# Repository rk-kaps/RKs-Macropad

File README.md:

<h1 align="center">RKs Macropad</h1>

<p align="center">
  Welcome to RKs Macropad, my custom 3D printed Macropad that runs KMK firmware.
</p>

<hr>
<h2>PCB & Schematic</h2>
<p align="center">
  
  <br><em>PCB Layout (KiCad)</em>
</p>
<p align="center">
  
  <br><em>Schematic</em>
</p>
<p align="center">
  
  <br><em>PCB 3D Render</em>
</p>

<h2>Motivation</h2>
<ul>>
MacroPad began as a simple rotary encoder-based volume controller. It evolved into a fully-featured macropad focused on:

Speeding up workflows
Reducing repetitive actions
Providing intuitive visual feedback
Maximizing functionality within hardware constraints
</ul>
</h2>
<h2> Project Highlights  </h2>
<ul>
- Efficient use of limited GPIO resources  
- Custom analog decoding for rotary encoder  
- Integration of hardware + firmware + UI design  
- Fully functional productivity tool
</ul>
<hr>

<h2>Bill of Materials:</h2>

<ul>
  <li>1x Rks Macropad PCB</li>
  <li>1x XIAO-PR2040-DIP</li>
  <li>1x EC11 rotary encoder</li>
  <li>11x Cherry MX (or equivalent) keyswitches</li>
  <li>11x Keycaps</li>
  <li>12x 1N4148 Throughhole diodes</li>
  <li>1x 0.91 inch OLED display (SSD1306 I2C 0.91 128x32)</li>
  <li>4x Cap head M3x16 machine screws</li>
  <li>1x 3D printed shell top half</li>
  <li>1x 3D printed shell bottom half</li>
</ul>

<p>
  small amount of spare wire apprx. 50mm worth.
</p>
<hr>
<h2>Instructions for Assembly</h2>
<ol>
  <li>Solder RP2040 directly onto the PCB without a header.</li>
  <li>Solder on diodes aligning with the silkscreen.</li>
  <li>Solder Cherry MX switches to board.</li>
  <li>
    Solder breakout cables to the spare 4 pins near the RP2040 — these will be used to wire to the OLED display.
    Make these breakout cables ~2" to allow for easier soldering.
  </li>
  <li>
    Clamshell the base around the PCB, passing the breakout cables through the small hole in the gap for the display
    in the top half of the case, then use the M3x16 machine screws to clamp the assembly together.
  </li>
  <li>Solder display to the breakout cables.</li>
  <li>Use double-sided tape or a light adhesive to hold the OLED into its holder.</li>
</ol>
<hr>
<h2>Acknowledgements</h2>
<ul>
- KMK Firmware Community  
- Good people of Hack Club
</ul>
<hr>

<h2>Instructions for Assembly:</h2>

<ol>
  <li>Solder RP2040 directly onto the pcb without a header.</li>
  <li>Solder on Diodes aligning with the slikscreen.</li>
  <li>Solder CherryMX switches to board.</li>
  <li>
    Solder breakout cables to the spare 4 pins near the RP2040, these will be used to wire to the OLED display.
    Make these breakout cables ~2" to allow for easier soledering.
  </li>
  <li>
    Clamshell the base around the PCB, passing the breakout cables through the small hole in the gap for the display
    in the top half of the case, then use the M3x16 machine screws to clamp the assembly together.
  </li>

  <li>Solder display to the breakout cables</li>
  <li>Use double-sided tape or a light adhesive to hold the OLED into its holder,.</li>

<h2> Acknowledgements  </h2>
<ul>
- KMK Firmware Community  
- Good people of Hack Club</ul>

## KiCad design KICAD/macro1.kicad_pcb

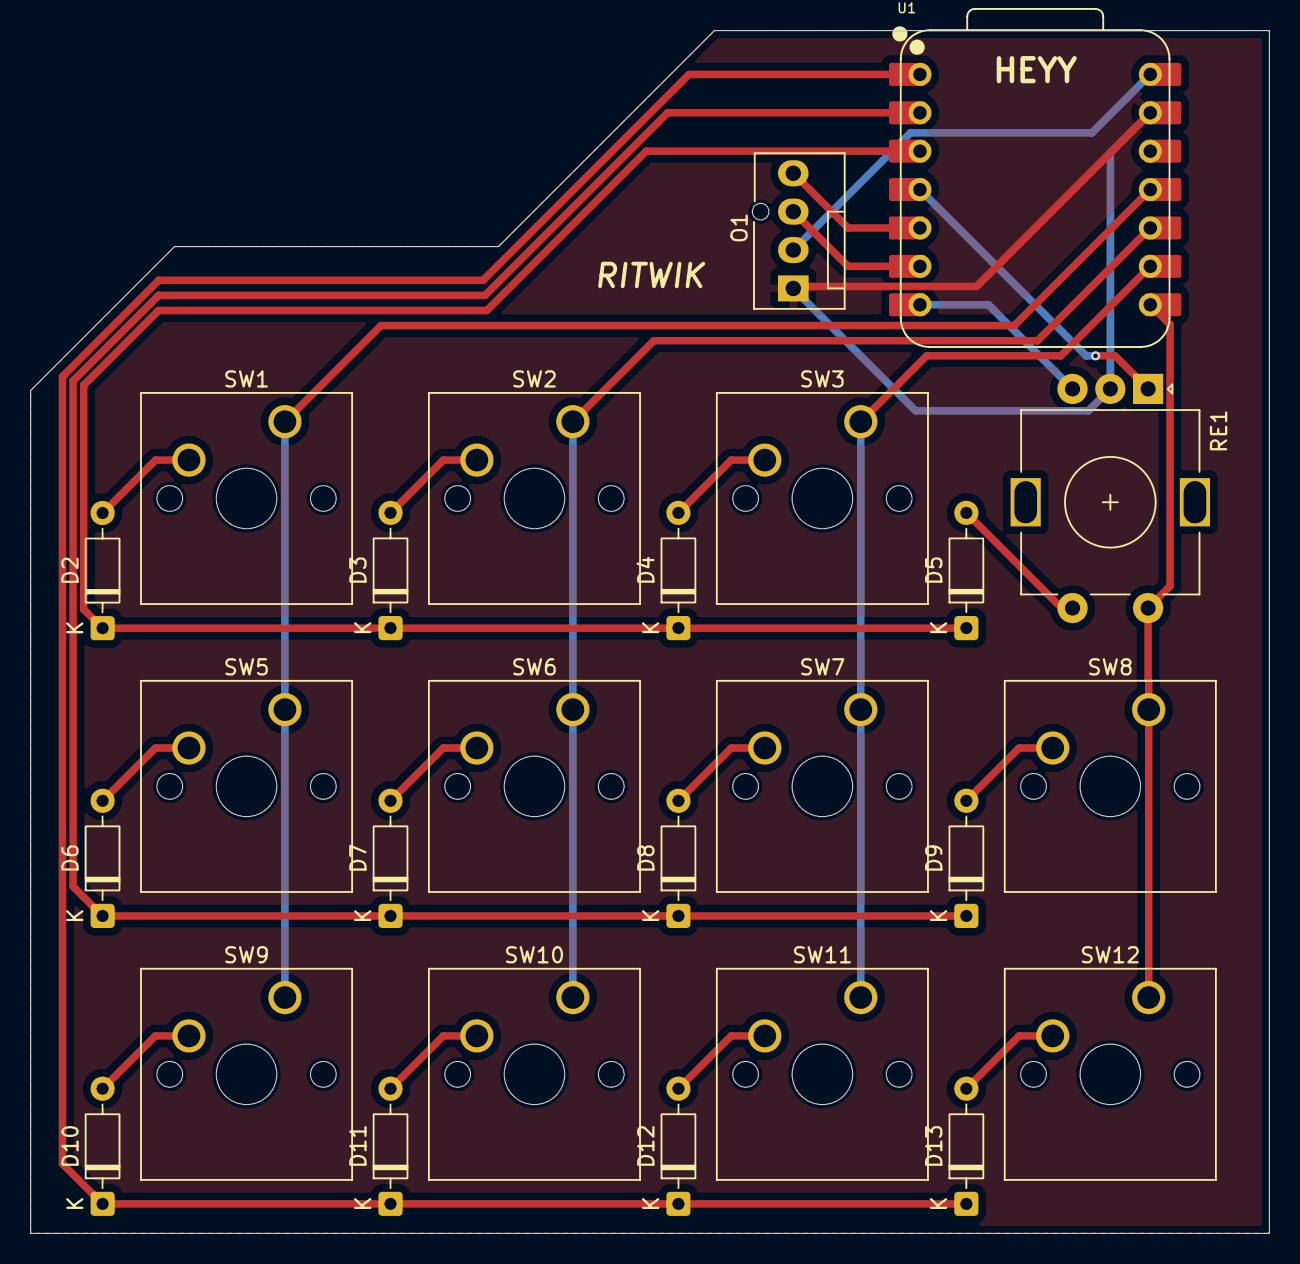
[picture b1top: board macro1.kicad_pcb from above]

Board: 2 copper layers, 82.0 x 79.6 mm, 26 parts (0 on the bottom side), 25 nets.

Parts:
D2, D3, D4, D5, D6, D7, D8, D9, D10, D11, D12, D13: 1N4148; D_DO-35_SOD27_P7.62mm_Horizontal
O1: FanPinHeader_1x04_P2.54mm_Vertical
RE1: RotaryEncoder_Alps_EC11E-Switch_Vertical_H20mm
SW1, SW2, SW3, SW5, SW6, SW7, SW8, SW9, SW10, SW11, SW12: SW_Push_45deg; SW_Cherry_MX_1.00u_PCB
U1: XIAO-RP2040-DIP

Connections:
+5V: O1.2 (VCC), U1.14 (VBUS)
Column 0: SW1.1, SW5.1, SW9.1, U1.11 (GPIO3/MOSI)
Column 1: SW2.1, SW6.1, SW10.1, U1.10 (GPIO4/MISO)
Column 2: SW3.1, SW7.1, SW11.1, U1.9 (GPIO2/SCK)
Column 3: RE1.S2 (SW), SW8.1, SW12.1, U1.8 (GPIO1/RX)
GND: O1.1 (GND), RE1.C, U1.13 (GND)
unnamed: D2.2 (A), SW1.2
unnamed: D3.2 (A), SW2.2
unnamed: D4.2 (A), SW3.2
unnamed: D5.2 (A), RE1.S1 (SW)
unnamed: D6.2 (A), SW5.2
unnamed: D7.2 (A), SW6.2
unnamed: D8.2 (A), SW7.2
unnamed: D9.2 (A), SW8.2
unnamed: D10.2 (A), SW9.2
unnamed: D11.2 (A), SW10.2
unnamed: D12.2 (A), SW11.2
unnamed: D13.2 (A), SW12.2
unnamed: O1.3 (SCL), U1.6 (GPIO7/SCL)
unnamed: O1.4 (SDA), U1.5 (GPIO6/SDA)
unnamed: RE1.B, U1.7 (GPIO0/TX)
unnamed: RE1.A, U1.4 (GPIO29/ADC3/A3)
Row 0: D2.1 (K), D3.1 (K), D4.1 (K), D5.1 (K), U1.3 (GPIO28/ADC2/A2)
Row 1: D6.1 (K), D7.1 (K), D8.1 (K), D9.1 (K), U1.2 (GPIO27/ADC1/A1)
Row 2: D10.1 (K), D11.1 (K), D12.1 (K), D13.1 (K), U1.1 (GPIO26/ADC0/A0)

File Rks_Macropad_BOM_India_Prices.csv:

Ref,Component,Manufacturer,Qty,Unit Price (₹),Total (₹),Store,Link
PCB,Rks Macropad PCB,Custom,1,250,250,JLCPCB,https://jlcpcb.com
MCU,XIAO-RP2040-DIP,Seeed Studio,1,914,914,Robocraze,https://robocraze.com/products/seeed-studio-xiao-rp2040-deve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
ENC,EC11 Rotary Encoder w/ Push Button,Hongyan,1,52,52,Robu.in,https://robu.in/product/hongyan-ec11h-7ce15p1zy15f7-rotary-e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
SW,Cherry MX RGB Switch (pack of 10),Cherry,2,350,700,Meckeys,https://meckeys.com/shop/accessories/keyboard-accessories/ke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
KP,Keycaps MX compatible (set),Generic,1,499,499,Meckeys,https://meckeys.com/category/accessories/keyboard-accessorie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
D,1N4148 Through-hole Diode,OnSemi,12,1,12,Robu.in,https://robu.in/product/diode-1n4148/
OLED,"0.91"" OLED SSD1306 I2C 128x32",Generic,1,149,149,Robu.in,https://robu.in/product/0-91-inch-128x32-i2c-iic-serial-blue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
SCR,Cap Head M3x16 Allen Bolt (12 pcs),EasyMech,1,89,89,Robu.in,https://robu.in/product/easymech-set-m3-x-16mm-socket-head-c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
SHL-T,3D Printed Shell - Top Half,Self-printed,1,150,150,3Ding.in,https://www.3ding.in
SHL-B,3D Printed Shell - Bottom Half,Self-printed,1,150,150,3Ding.in,https://www.3ding.in
,,,,TOTAL,2965,,

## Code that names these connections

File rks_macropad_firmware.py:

print("Starting Rks Macropad")
import board
import busio
import digitalio
import time
from kmk.kmk_keyboard import KMKKeyboard
from kmk.keys import KC
from kmk.scanners import DiodeOrientation
from kmk.extensions.media_keys import MediaKeys
from kmk.modules.layers import Layers
import adafruit_ssd1306

# --- OLED Setup ---
# IMPORTANT: Due to the display orientation in this build, the OLED is connected
# via breakout wires (not directly plugged into the PCB).
# Wire connections from Waveshare RP2040-Zero to SSD1306 OLED:
#   VCC  -> 3.3V pin on RP2040-Zero  ⚠️ DO NOT use 5V/VBUS — will damage the display
#   GND  -> GND
#   SDA  -> GP6
#   SCL  -> GP7
i2c = busio.I2C(board.GP7, board.GP6)  # SCL=GP7, SDA=GP6
oled = adafruit_ssd1306.SSD1306_I2C(128, 32, i2c)

# --- Layer Names ---
LAYER_NAMES = ["Main", "Onshape", "Reaper"]
current_layer = 0

# --- Key Labels per layer ---
LAYER_LABELS = [
    [
        ["PREV", "NEXT", "PLAY", "LYR"],
        ["SNIP", "SHOW", "LOCK", "EMOJI"],
        ["RUN",  "TABS", "MUTE", "DESK"],
    ],
    [
        ["SKTCH", "EXVW", "FIT",  "LYR"],
        ["FRONT", "RGHT", "TOP",  "MATE"],
        ["ZOOM+", "ZOOM-","ROT",  "LYR"],
    ],
    [
        ["PLAY", "STOP", "REC",  "LYR"],
        ["MUTE", "SOLO", "LOOP", "QTSE"],
        ["ZM+",  "ZM-",  "TAP",  "LYR"],
    ],
]

# --- Key Actions per layer ---
LAYER_ACTIONS = [
    [
        "Prev Track", "Next Track", "Play/Pause", "Next Layer",
        "Snip", "Show Desktop", "Lock", "Emoji",
        "Run", "Task View", "Mute", "New Desktop",
    ],
    [
        "Sketch", "Exit View", "Fit All", "Next Layer",
        "Front View", "Right View", "Top View", "Mate",
        "Zoom In", "Zoom Out", "Rotate", "Next Layer",
    ],
    [
        "Play", "Stop", "Record", "Next Layer",
        "Mute Track", "Solo Track", "Toggle Loop", "Quantise",
        "Zoom In", "Zoom Out", "Tap Tempo", "Next Layer",
    ],
]

TIMEOUT = 1
DISPLAY_INTERVAL = 0.5

last_action_time = None
last_display_update = 0
pending_action = None
pending_is_volume = False
volume_direction = None

def draw_static():
    oled.fill(0)
    layer_label = LAYER_NAMES[current_layer]
    oled.text(layer_label, 0, 0, 1)
    oled.fill_rect(0, 9, 128, 1, 1)
    labels = LAYER_LABELS[current_layer]
    for row in range(3):
        for col in range(4):
            x = col * 32
            y = 11 + row * 7
            oled.text(labels[row][col], x, y, 1)
    oled.show()

def show_action(label):
    global last_action_time
    oled.fill(0)
    char_width = 12
    text_width = len(label) * char_width
    x = max(0, (128 - text_width) // 2)
    y = 8
    oled.text(label, x, y, 1, size=2)
    oled.show()
    last_action_time = time.monotonic()

def show_volume(direction):
    oled.fill(0)
    label = "Vol Up" if direction == "up" else "Vol Down"
    char_width = 12
    text_width = len(label) * char_width
    x = max(0, (128 - text_width) // 2)
    y = 8
    oled.text(label, x, y, 1, size=2)
    oled.show()

def show_layer_name(name):
    oled.fill(0)
    char_w = 12
    text_w = len(name) * char_w
    x = max(0, (128 - text_w) // 2)
    oled.text(name, x, 8, 1, size=2)
    oled.show()

draw_static()

# --- Keyboard Setup ---
# Pin mapping verified from macro1.kicad_pcb / macro1.kicad_sch:
#   Col 0 -> GPIO4  (GP4)
#   Col 1 -> GPIO3  (GP3)
#   Col 2 -> GPIO2  (GP2)
#   Col 3 -> GPIO1  (GP1)
#   Row 0 -> GPIO28 (GP28)
#   Row 1 -> GPIO27 (GP27)
#   Row 2 -> GPIO26 (GP26)
# Matrix: 3 rows x 4 cols = 12 keys
keyboard = KMKKeyboard()
keyboard.col_pins = (board.GP4, board.GP3, board.GP2, board.GP1)
keyboard.row_pins = (board.GP28, board.GP27, board.GP26)
keyboard.diode_orientation = DiodeOrientation.COL2ROW
keyboard.extensions.append(MediaKeys())

layers_mod = Layers()
keyboard.modules.append(layers_mod)

LYR_MAIN    = KC.TO(0)
LYR_ONSHAPE = KC.TO(1)
LYR_REAPER  = KC.TO(2)

keyboard.keymap = [
    # Layer 0 - Main
    [
        KC.MPRV,                    KC.MNXT,           KC.MPLY,                 LYR_ONSHAPE,
        KC.LGUI(KC.LSFT(KC.S)),     KC.LGUI(KC.D),     KC.LGUI(KC.L),           KC.LGUI(KC.DOT),
        KC.LGUI(KC.R),              KC.LGUI(KC.TAB),   KC.MUTE,                 KC.LCTL(KC.LGUI(KC.D)),
    ],
    # Layer 1 - Onshape
    [
        KC.S,                       KC.E,              KC.F,                    LYR_REAPER,
        KC.LCTL(KC.NUM_1),          KC.LCTL(KC.NUM_2), KC.LCTL(KC.NUM_3),       KC.M,
        KC.LCTL(KC.EQUAL),          KC.LCTL(KC.MINUS), KC.LCTL(KC.R),           LYR_REAPER,
    ],
    # Layer 2 - Reaper
    [
        KC.SPACE,                   KC.LCTL(KC.SPACE), KC.LCTL(KC.LSFT(KC.R)), LYR_MAIN,
        KC.F6,                      KC.F8,             KC.LCTL(KC.L),           KC.LCTL(KC.LSFT(KC.Q)),
        KC.LCTL(KC.EQUAL),          KC.LCTL(KC.MINUS), KC.LALT(KC.LSFT(KC.T)), LYR_MAIN,
    ],
]

# --- Encoder Setup ---
# Pin mapping verified from macro1.kicad_pcb:
#   Pad A (CLK) -> GPIO29 -> GP29
#   Pad B (DT)  -> GPIO0  -> GP0
#   Pad C       -> GND (common ground)
#   Pad S2      -> Column 3 (encoder push handled as a matrix key)
clk = digitalio.DigitalInOut(board.GP29)
clk.direction = digitalio.Direction.INPUT
clk.pull = digitalio.Pull.UP

dt = digitalio.DigitalInOut(board.GP0)
dt.direction = digitalio.Direction.INPUT
dt.pull = digitalio.Pull.UP

ENCODER_TABLE = {
    (1, 1, 0, 1): -1,
    (0, 1, 0, 0): -1,
    (0, 0, 1, 0): -1,
    (1, 0, 1, 1): -1,
    (1, 1, 1, 0): +1,
    (1, 0, 0, 0): +1,
    (0, 0, 0, 1): +1,
    (0, 1, 1, 1): +1,
}

last_clk = int(clk.value)
last_dt = int(dt.value)
accumulated = 0

_original_main_loop = keyboard._main_loop

def patched_main_loop():
    global last_clk, last_dt, accumulated
    global last_display_update, pending_action, last_action_time
    global pending_is_volume, volume_direction, current_layer

    now = time.monotonic()

    # --- Sync current_layer from KMK ---
    new_layer = keyboard.active_layers[0]
    if new_layer != current_layer:
        current_layer = new_layer
        show_layer_name(LAYER_NAMES[current_layer])
        last_action_time = now

    # --- Encoder ---
    cur_clk = int(clk.value)
    cur_dt = int(dt.value)
    state = (last_clk, last_dt, cur_clk, cur_dt)
    direction = ENCODER_TABLE.get(state, 0)
    if direction != 0:
        accumulated += direction
    last_clk = cur_clk
    last_dt = cur_dt

    if accumulated >= 2:
        if current_layer == 1:
            keyboard.tap_key(KC.LSFT(KC.Z))
            pending_action = "Zoom In"
            pending_is_volume = False
        else:
            keyboard.tap_key(KC.VOLU)
            pending_action = "Vol Up"
            pending_is_volume = True
            volume_direction = "up"
        accumulated = 0
    elif accumulated <= -2:
        if current_layer == 1:
            keyboard.tap_key(KC.Z)
            pending_action = "Zoom Out"
            pending_is_volume = False
        else:
            keyboard.tap_key(KC.VOLD)
            pending_action = "Vol Down"
            pending_is_volume = True
            volume_direction = "down"
        accumulated = 0

    # --- Key presses ---
    for key in keyboard.keys_pressed:
        try:
            idx = list(keyboard.keymap[current_layer]).index(key)
            action = LAYER_ACTIONS[current_layer][idx]
            if action != "Next Layer":
                pending_action = action
                pending_is_volume = False
        except (ValueError, IndexError):
            pass

    # --- Display update ---
    if now - last_display_update >= DISPLAY_INTERVAL:
        if pending_action is not None:
            if pending_is_volume:
                show_volume(volume_direction)
            else:
                show_action(pending_action)
            pending_action = None
            last_action_time = now
        elif last_action_time is not None and (now - last_action_time) > TIMEOUT:
            last_action_time = None
            draw_static()
        last_display_update = now

    return _original_main_loop()

keyboard._main_loop = patched_main_loop
keyboard.go()

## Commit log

2026-03-29 Fix Onshape link
    Updated Onshape document link
2026-03-30 Rename Exploded.png to deconstructed_view.png
2026-04-04 Update README.md
    Added detailed assembly instructions and acknowledgements.
